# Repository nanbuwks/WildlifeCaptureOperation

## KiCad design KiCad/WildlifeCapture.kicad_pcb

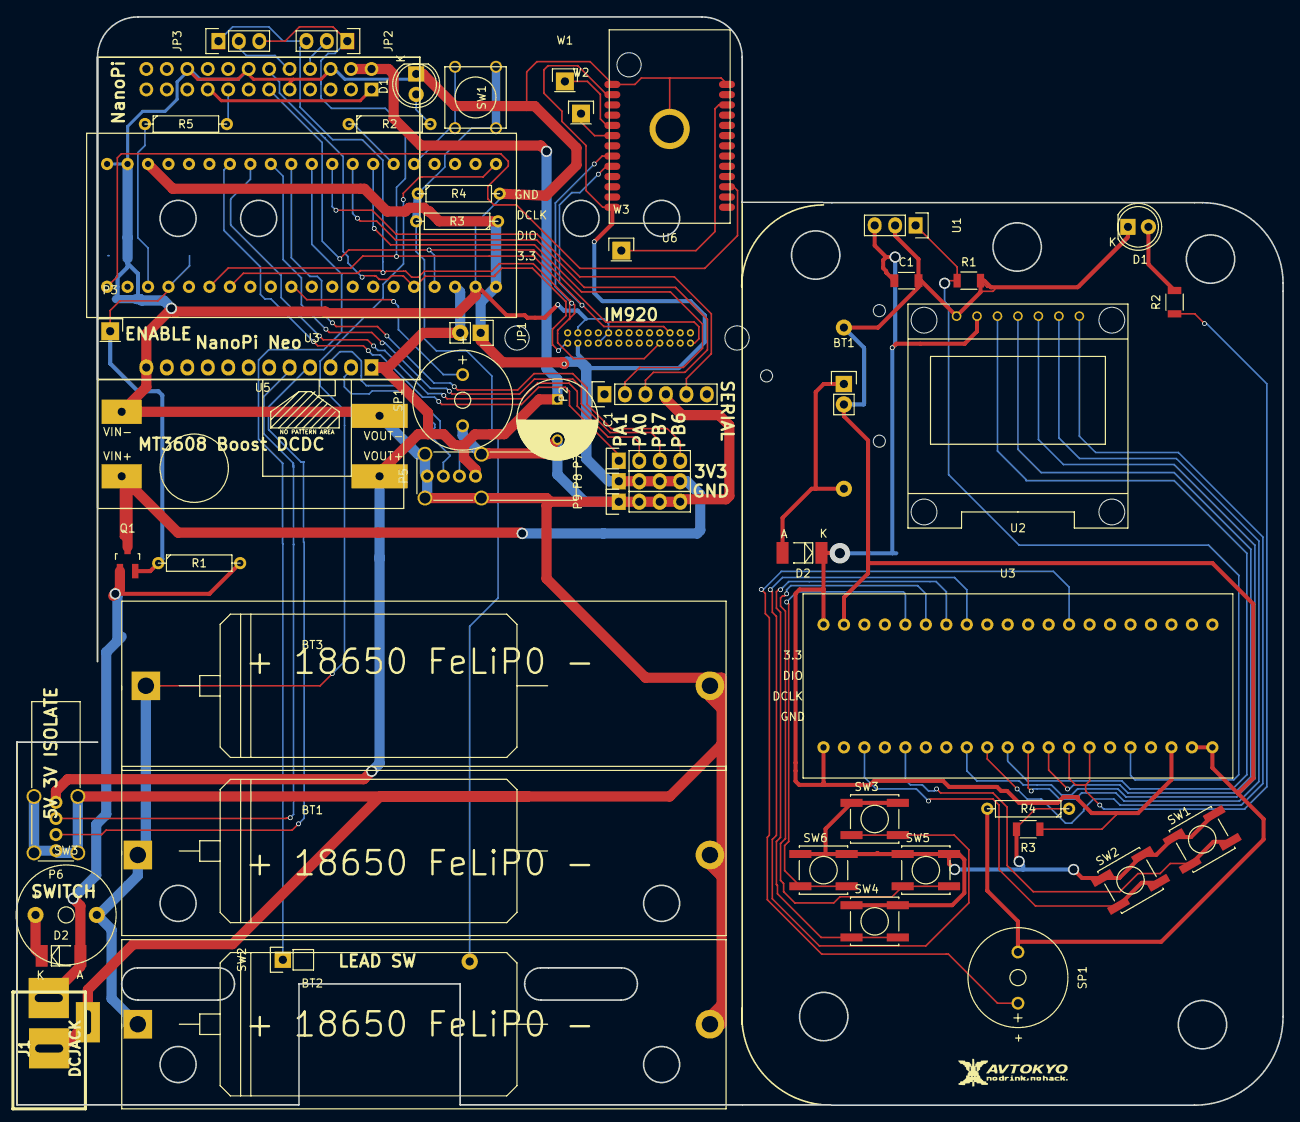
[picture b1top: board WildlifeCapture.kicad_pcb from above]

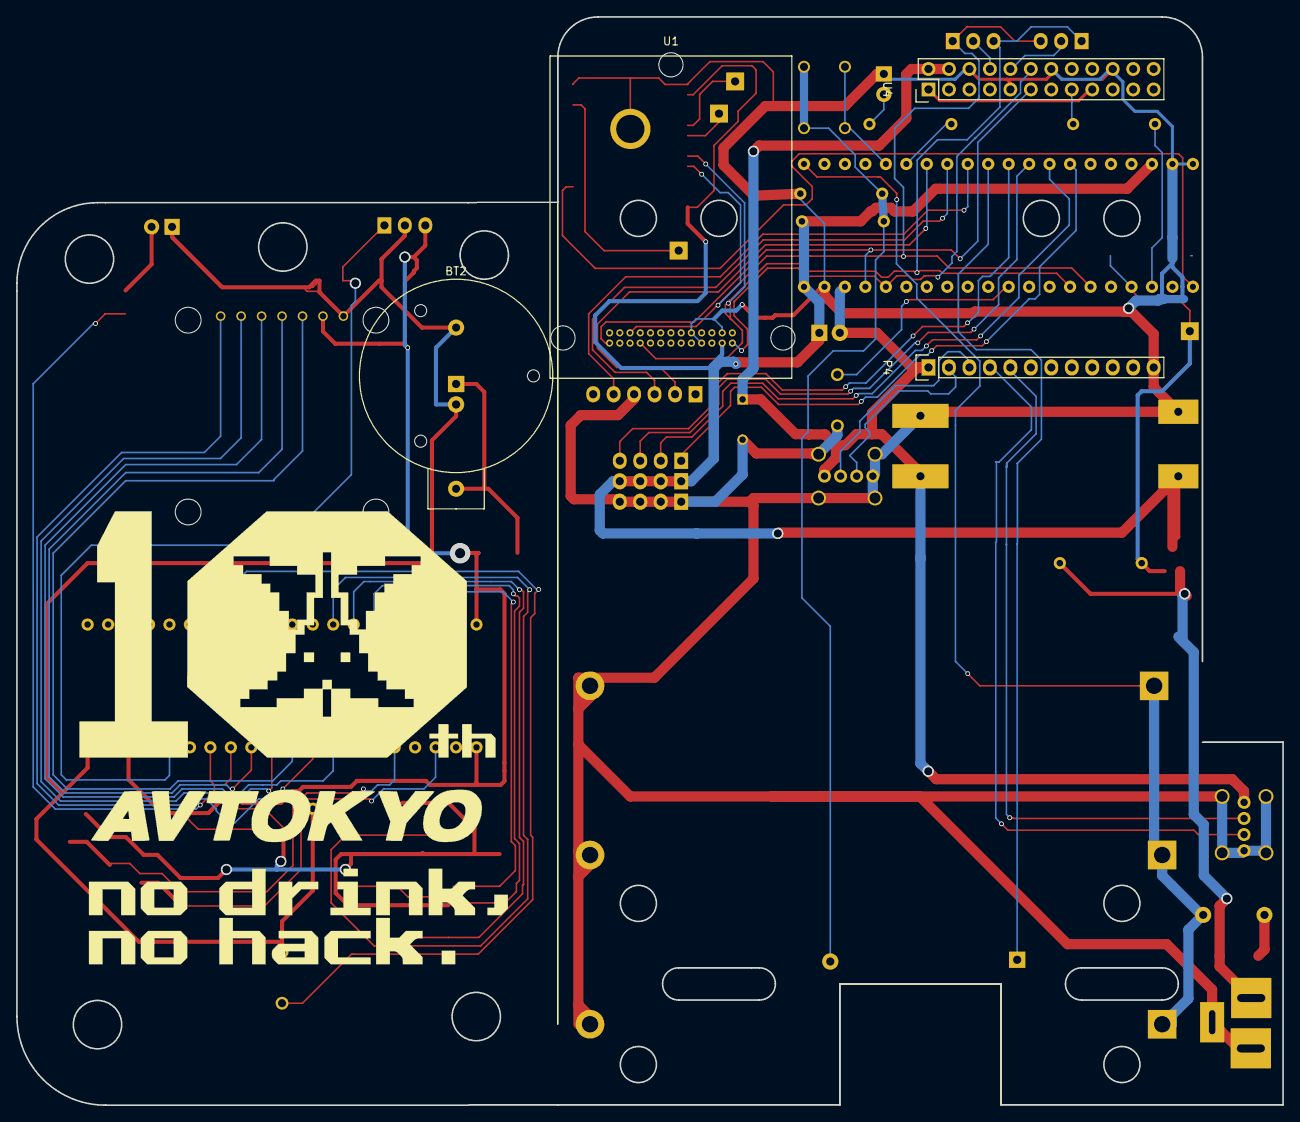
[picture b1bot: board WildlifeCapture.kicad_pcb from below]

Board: 2 copper layers, 157.1 x 135.1 mm, 55 parts (4 on the bottom side), 55 nets.

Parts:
BT1: Battery; Pin_Header_Straight_1x02
BT1#2, BT2#2, BT3: Battery; 18650BatteryCase
BT2: Battery; BATTERY_CR2032_CH25-2032LF_CONFORTABLE
C1: C; C_1206
C1#2: CP1; C_Radial_D10_L13_P5
D1, D1#2: LED; LED-5MM
D2, D2#2: DIODESCH; MELF_Standard
J1: DCJACK
JP1: JUMPER; Pin_Header_Straight_1x02
JP2, JP3: JUMPER3; Pin_Header_Straight_1x03
P2: GPS; Pin_Header_Straight_1x06
P3: EN; Pin_Header_Straight_1x01
P4: NanoPi_USB/Audio/IR; Pin_Header_Straight_1x12
P5, P6: USB_A; USB_A_Vertical
P7: SERVICE; Pin_Header_Straight_1x04
P8: VCC; Pin_Header_Straight_1x04
P9: GND; Pin_Header_Straight_1x04
Q1: MOSFET_P; SOT-23_Handsoldering
R1: 10kΩ; R_1206
R1#2, R5: R; R4
R2: 180Ω; R_1206
R2#2: 180Ω; R4
R3: 2.7kΩ; R_1206
R3#2: 2.7kΩ; R4
R4, R4#2: OPEN; R4
SP1, SP1#2: SPEAKER; MagneticBuzzer_ProSignal_ABT-410-RC
SW1: A; SW_SPST_EVPBF
SW1#2: A; SW_PUSH_SMALL_1mmHOLE
SW2: B; SW_SPST_EVPBF
SW2#2: LEADSW; Pin_Header_Straight_1x02
SW3: UP; SW_SPST_EVPBF
SW3#2: SWITCH_INV; Buzzer_12x9.5RM7.6
SW4: DOWN; SW_SPST_EVPBF
SW5: LEFT; SW_SPST_EVPBF
SW6: RIGHT; SW_SPST_EVPBF
U1: PhotoReciever_GP1USC4XQS_SHARP; Pin_Header_Straight_1x03
U1#2: IM920_interplan
U2: OLED_0.96in_SPI
U3: STM32F103C8T6MinimumDevelopBoard; STM32F103C8T6ARMMiniSystemDevboard_RobotDyn
U3#2: STM32F103C8T6MinimumDevelopBoard
U4: RASPBERRYPI_GPIO_40; Pin_Header_Straight_2x12
U5: MT3608
U6: ES920LR_LPWA_EASEL; ES920_LPWA_EASEL
W1, W2, W3: TEST_1P; Pin_Header_Straight_1x01

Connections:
+3V3: C1.1, D2.2, R3.1, U1.3, U2.2, U3.20, U3.21, U3.38, U4.1, U4.17
+5V: C1#2.1, JP1.2, P4.1, P5.1, P6.1, U3#2.18, U4.2, U4.4, U5.3
+BATT: D2#2.2, J1.1, JP1.1, P8.1, P8.2, P8.3, P8.4, R1#2.2, R3#2.1, U1#2.23, U3#2.20, U3#2.38, U6.2, U6.13
GND: BT1.2, BT1#2.2, BT2.2, BT2#2.2, BT3.2, C1.2, C1#2.2, D1.1, D1#2.1, J1.2, J1.3, P2.4, P4.12, P5.4, P5.5, P6.4, P6.5, P9.1, P9.2, P9.3, P9.4, R1.2, R4.2, R4#2.2, SP1.1, SP1#2.1, U1.2, U1#2.18, U1#2.19, U1#2.24, U2.1, U3.19, U3.39, U3.40, U3#2.19, U3#2.39, U3#2.40, U4.6, U4.9, U4.14, U4.20, U5.2, U5.4, U6.1, U6.26, U6.27
unnamed: BT1.1, BT1#2.1, BT2.1, BT2#2.1, BT3.1, D2.1, SW3#2.2, U3#2.21
unnamed: D1.2, D1#2.2, R2.2, R2#2.2
unnamed: D2#2.1, SW3#2.1
unnamed: JP2.1, JP3.3, U1#2.6, U3#2.6, U6.9
unnamed: JP2.2, U4.8
unnamed: JP2.3, JP3.1, U1#2.7, U3#2.7, U6.8
unnamed: JP3.2, U4.10
unnamed: P2.2, U3#2.27
unnamed: P2.3, U3#2.28
unnamed: P2.5, U3#2.29
unnamed: P4.2, P5.3
unnamed: P4.3, P5.2
unnamed: P4.4, P6.3
unnamed: P4.5, P6.2
unnamed: P7.1, U3#2.34
unnamed: P7.2, U3#2.33
unnamed: P7.3, U3#2.32
unnamed: P7.4, U3#2.31
unnamed: R1#2.1, U3#2.4
unnamed: R1.1, U1.1, U3.36
unnamed: R2.1, R2#2.1, U3.33, U3.34, U3#2.26
unnamed: R3.2, R3#2.2, R4.1, R4#2.1, SW1.1, SW1#2.1, SW2.1, SW2#2.2, SW3.1, SW4.1, SW5.1, SW6.1
unnamed: R5.1, U3#2.3
unnamed: R5.2, U4.15
unnamed: SP1.2, SP1#2.2, U3.8, U3#2.10
unnamed: SW1.2, SW1#2.2, U3.25, U3#2.25
unnamed: SW2#2.1, U3#2.30
unnamed: SW2.2, U3.23
unnamed: SW3.2, U3.13
unnamed: SW4.2, U3.14
unnamed: SW5.2, U3.15
unnamed: SW6.2, U3.16
unnamed: U1#2.1, U3#2.17, U4.11
unnamed: U1#2.25, U3#2.16, U4.12
unnamed: U2.3, U3.30, U3#2.35
unnamed: U2.4, U3.32, U3#2.36
unnamed: U2.5, U3.28
unnamed: U2.6, U3.31
unnamed: U2.7, U3.29
unnamed: U3.1, U3#2.1, U6.16
unnamed: U3.2, U3#2.2
unnamed: U3.5, U3#2.5
unnamed: U3.9, U3#2.9
unnamed: U3.11, U3#2.11
unnamed: U3.12, U3#2.12
unnamed: U3.22, U3#2.22
unnamed: U3.24, U3#2.24
unnamed: U3.37, U3#2.37
unnamed: U6.5, W1.1
unnamed: U6.6, W2.1
unnamed: U6.24, W3.1

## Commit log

2017-10-10 Change to Take 2
2018-01-03 Change to Take 3
